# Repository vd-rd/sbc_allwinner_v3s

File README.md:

# Allwinner V3s SBC

This board embeds a SIP (single core 1GHz Cortex-A7 with 64MB DDR2) with AXP203 PMIC, IO headers and microSD/eMMC storage.

Board overview (draft):
[TBD]

## Board features
| Characteristic | Description |
| --- | --- |
| Dimensions | 60mm x 40mm |
| Processor | Allwinner V3s Cortex-A7 @1GHz |
| Oscillators | 32.768kHz slow click, 24MHz main clock |
| RAM | 512Mb embedded DDR2 memory |
| Storage | SPI Flash/microSD |
| USB | 1 microUSB OTG |
| Ethernet | 10/100M PHY with pins on header |
| Supply | Power path between USB/Vin/Battery, 5V max |

## Notes and observations

### Expansions
The board features a number of connectors. They expose various buses for expansions:
 * 1 SPI port
 * 2 UART ports
 * 1 I2C port
 * 2 ADC enabled pins
 * 18bit parallel LCD interface
 * Ethernet signals with status LEDs

The connectors are organized in consistent locations present on the other SBCs i have developed.
 * J100 connector - 2.54mm 2x18 header with standard Apollo IoT pinout
 * J200 connector - 1.27mm 2x04 header with ethernet signals
 * J300 connector - 1.27mm 2x05 header with analog audio I/O signals
 * J500 connector - 1.27mm 2x20 header with parallel LCD interface signals

Check expansions section for example daughter cards with added functionality

### Boot process
The board has two boot strategies depending on component configuration. If the SPI flash memory is not used, the BROM uses the MicroSD as boot source and loads UBoot from there.
If the SPI flash is populated, UBoot with a minimal Kernel and Busybox can be stored as recovery environment or main application.

### LCD connector
Most of port D signals are mapped to the LCD connector. if LCD is not used they can be muxed as GPIO or other functions upon editing the DT overlay.

### AXP203
AXP203 is pin to pin compatible with the more popular AXP209, so they can be easily swapped.

### 1.2V Rail
Two different 1.2V rails are provided to the CPU. This is a deliberate decision to allow fixed CPU internal rail at 1.2V and provide DVFS cappability to 1.2V rail for CPU core.

### Signals on headers
All the signals on the headers, with their initial functions are detailed on the silkscreen on the bottom layer

### Battery usage
The board schematic uses a Diodes AP9211 battery protection IC for safety protections when used toghether with a LiIon battery. If a battery pack with embedded protection and thermistor is used, TH1 and AP9211 can be left unpopulated.

### Expansions
 The board can be combined with several predefined capes that add functionality.
 * [LCD cape](https://github.com/vd-rd/hw_cape_lcd) can be used to add a 3inch LCD/Touch with 800x480px resolution.
 * [GPS cape](https://github.com/vd-rd/hw_cape_gps) adds GPS/GNSS/GLONAS capabilities
 * [GSM cape](https://github.com/vd-rd/hw_cape_gsm) adds GPRS connectivity. 

## Resources
You can find all necesary information to build or evaluate the module here:
   - [View 3D board render](https://a360.co/2GTPupk)
   - [Fabrication files](https://github.com/vd-rd/sbc_alw_v3s/releases)

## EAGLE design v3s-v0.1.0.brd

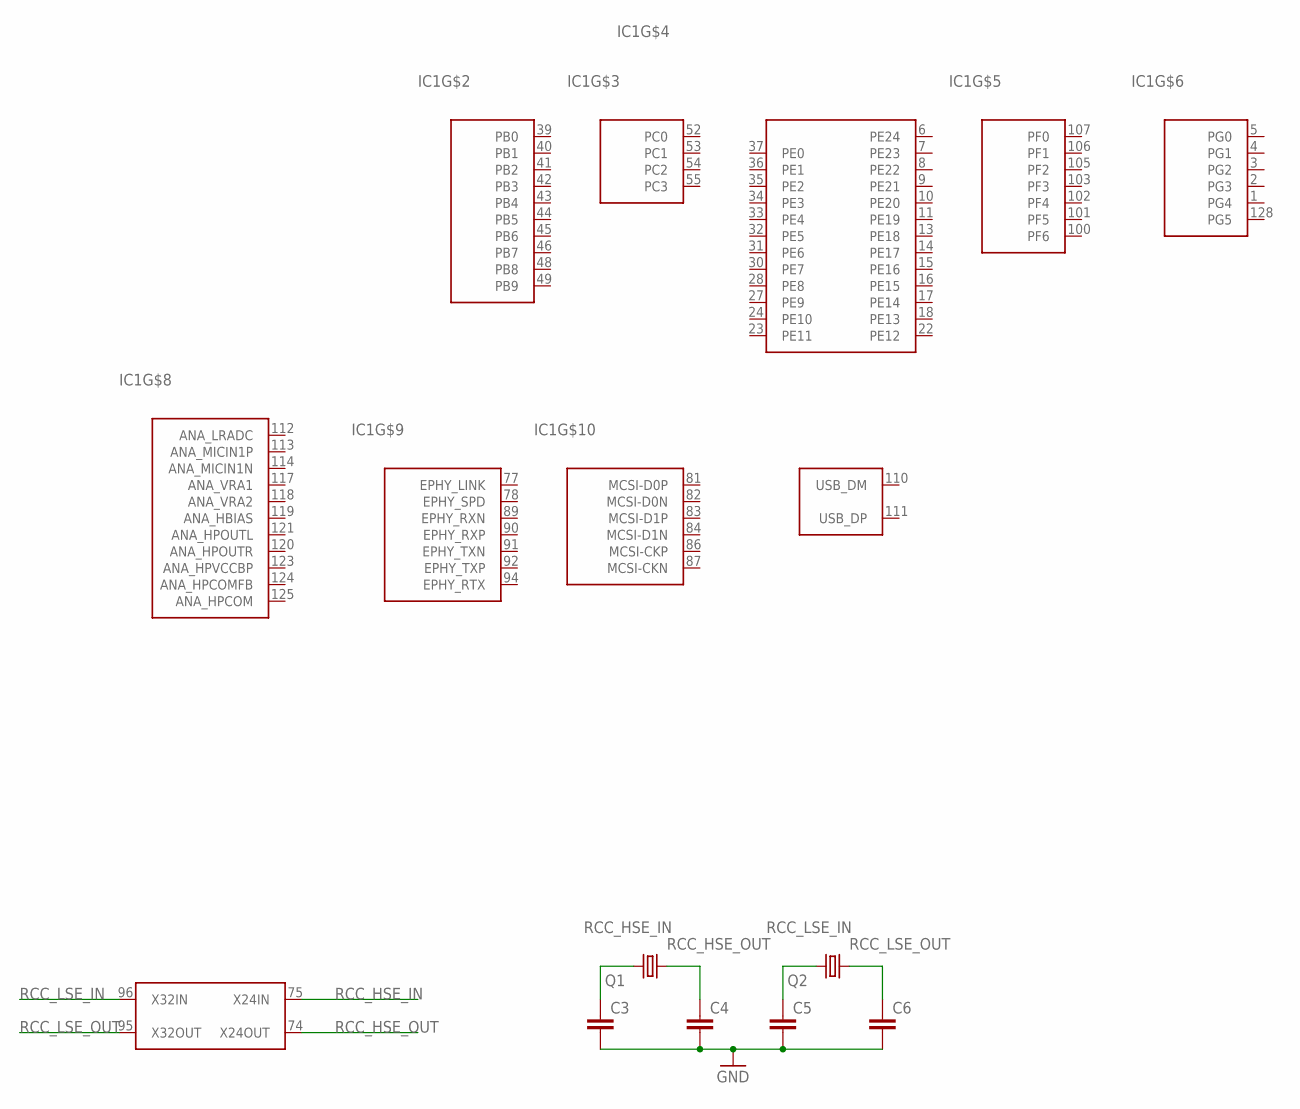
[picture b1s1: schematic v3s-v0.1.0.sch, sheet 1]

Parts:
C3, C4, C5, C6: C-EUC0402; C0402
IC1: V3S; QFP-128
Q1: KX-7; 3.2X2.5_KX-7
Q2: KX-327-NHF; 3.2X1.5

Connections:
GND: C3.2, C4.2, C5.2, C6.2; also elsewhere on the board
RCC_HSE_IN: C3.1, IC1.75 (X24IN), Q1.3 (2)
RCC_HSE_OUT: C4.1, IC1.74 (X24OUT), Q1.1
RCC_LSE_IN: C5.1, IC1.96 (X32IN), Q2.2
RCC_LSE_OUT: C6.1, IC1.95 (X32OUT), Q2.1

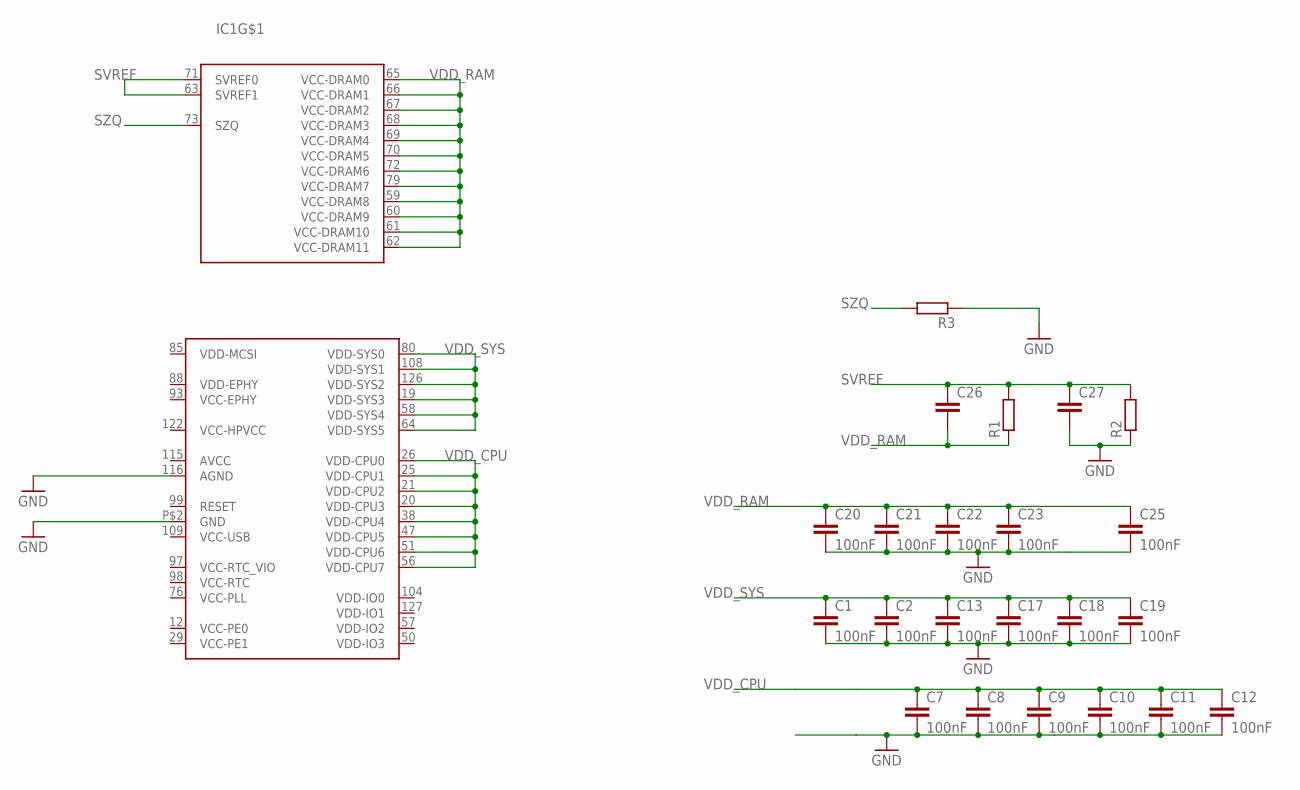
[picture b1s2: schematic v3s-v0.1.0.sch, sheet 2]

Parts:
C1, C2, C7, C8, C9, C10, C11, C12, C13, C17, C18, C19, C20, C21, C22, C23, C25: 100nF; C0402
C26, C27: C-EUC0402; C0402
IC1: V3S; QFP-128
R1, R2, R3: R-EU_R0402; R0402

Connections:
GND: C1.2, C2.2, C7.2, C8.2, C9.2, C10.2, C11.2, C12.2, C13.2, C17.2, C18.2, C19.2, C20.2, C21.2, C22.2, C23.2, C25.2, C27.2, IC1.116 (AGND), IC1.P$2 (GND), R2.1, R3.1; also elsewhere on the board
SVREF: C26.1, C27.1, IC1.63 (SVREF1), IC1.71 (SVREF0), R1.2, R2.2
SZQ: IC1.73 (SZQ), R3.2
VDD_CPU: C7.1, C8.1, C9.1, C10.1, C11.1, C12.1, IC1.20 (VDD-CPU3), IC1.21 (VDD-CPU2), IC1.25 (VDD-CPU1), IC1.26 (VDD-CPU0), IC1.38 (VDD-CPU4), IC1.47 (VDD-CPU5), IC1.51 (VDD-CPU6), IC1.56 (VDD-CPU7)
VDD_RAM: C20.1, C21.1, C22.1, C23.1, C25.1, C26.2, IC1.59 (VCC-DRAM8), IC1.60 (VCC-DRAM9), IC1.61 (VCC-DRAM10), IC1.62 (VCC-DRAM11), IC1.65 (VCC-DRAM0), IC1.66 (VCC-DRAM1), IC1.67 (VCC-DRAM2), IC1.68 (VCC-DRAM3), IC1.69 (VCC-DRAM4), IC1.70 (VCC-DRAM5), IC1.72 (VCC-DRAM6), IC1.79 (VCC-DRAM7), R1.1
VDD_SYS: C1.1, C2.1, C13.1, C17.1, C18.1, C19.1, IC1.19 (VDD-SYS3), IC1.58 (VDD-SYS4), IC1.64 (VDD-SYS5), IC1.80 (VDD-SYS0), IC1.108 (VDD-SYS1), IC1.126 (VDD-SYS2)

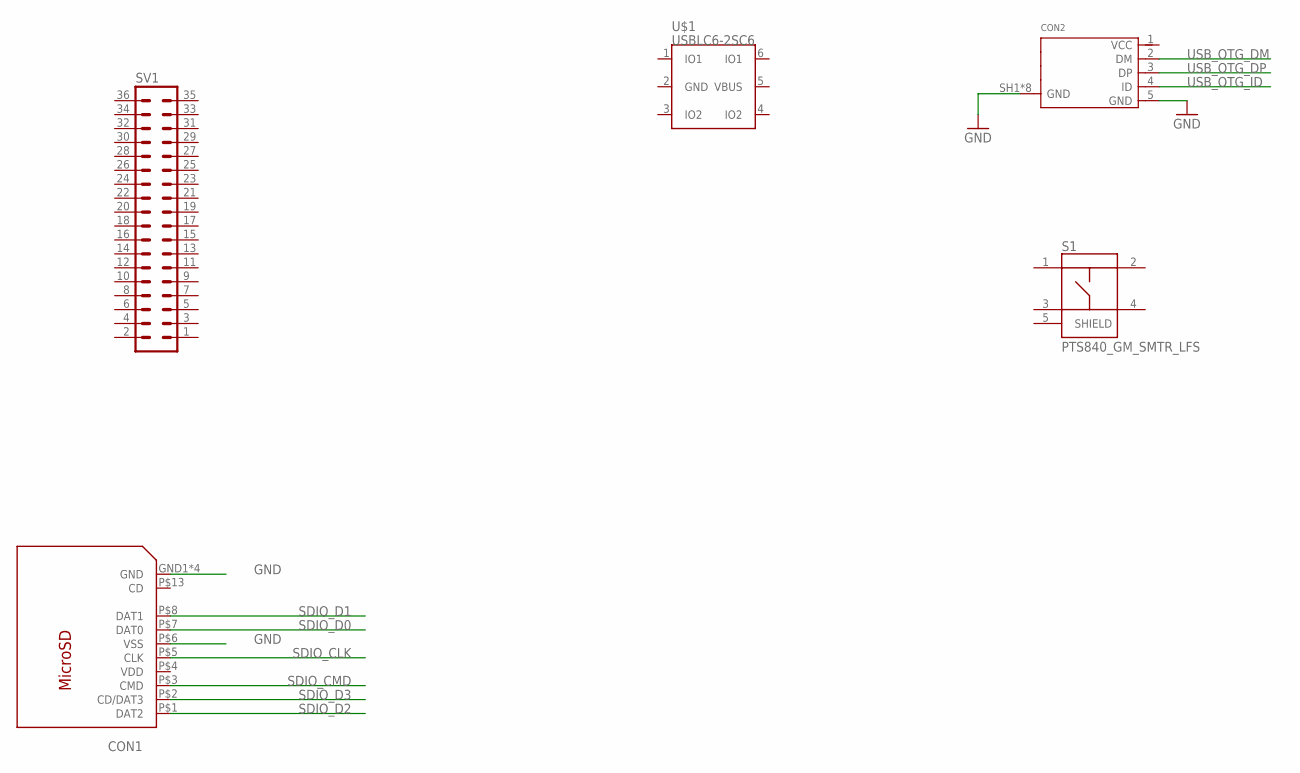
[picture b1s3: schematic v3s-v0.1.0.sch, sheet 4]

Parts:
CON1: 112J-TXAR; 112J
CON2: 10118194-0001LF; 10118194
S1: PTS840_GM_SMTR_LFS; SW_PTS840GMSMTRLFS
SV1: MA18-2
U$1: USBLC6-2SC6; SOT95P280X110-6

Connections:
GND: CON1.GND1 (GND), CON1.GND2 (GND), CON1.GND3 (GND), CON1.GND4 (GND), CON1.P$6 (VSS), CON2.5 (GND), CON2.SH1 (GND), CON2.SH2 (GND), CON2.SH3 (GND), CON2.SH4 (GND), CON2.SH5 (GND), CON2.SH6 (GND), CON2.SH7 (GND), CON2.SH8 (GND); also elsewhere on the board
SDIO_CLK: CON1.P$5 (CLK)
SDIO_CMD: CON1.P$3 (CMD)
SDIO_D0: CON1.P$7 (DAT0)
SDIO_D1: CON1.P$8 (DAT1)
SDIO_D2: CON1.P$1 (DAT2)
SDIO_D3: CON1.P$2 (CD/DAT3)
USB_OTG_DM: CON2.2 (DM)
USB_OTG_DP: CON2.3 (DP)
USB_OTG_ID: CON2.4 (ID)

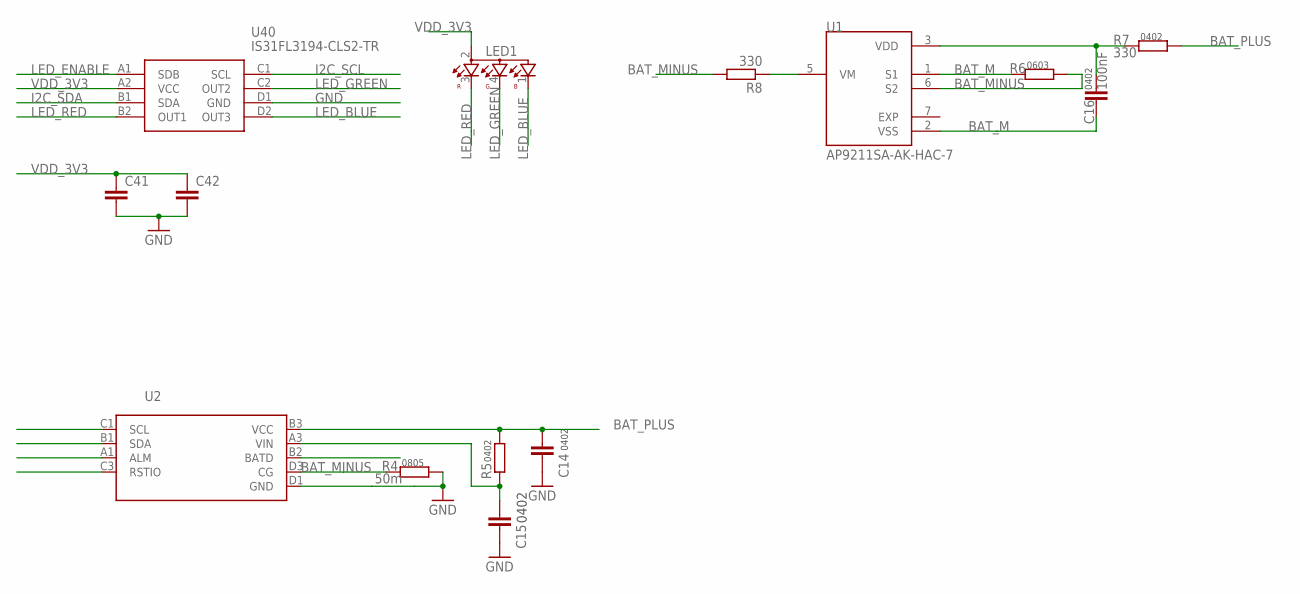
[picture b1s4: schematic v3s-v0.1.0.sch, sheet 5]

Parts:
C14, C15, C41, C42: C-EUC0402; C0402
C16: 100nF; C0402
LED1: OSTB1204C1E; 321015RGB
R4: 50m; R0805
R5: R-EU_R0402; R0402
R6: R-EU_R0603; R0603
R7, R8: 330; R0402
U1: AP9211SA-AK-HAC-7; DFN200X300X60-7N
U2: STC3115; BGA12C40P4X3_137X201X65
U40: IS31FL3194-CLS2-TR; BGA8C40P2X4_99X159X42

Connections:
BAT_M: C16.2, R6.2, U1.1 (S1), U1.2 (VSS)
BAT_MINUS: R4.2, R6.1, R8.2, U1.6 (S2), U2.D3 (CG)
BAT_PLUS: C14.1, R5.2, R7.1, U2.B3 (VCC)
EXP: U1.7 (EXP)
GND: C14.2, C15.2, C41.2, C42.2, R4.1, U2.D1 (GND), U40.D1 (GND); also elsewhere on the board
I2C_SCL: U40.C1 (SCL)
I2C_SDA: U40.B1 (SDA)
LED_BLUE: LED1.1, U40.D2 (OUT3)
LED_ENABLE: U40.A1 (SDB)
LED_GREEN: LED1.4, U40.C2 (OUT2)
LED_RED: LED1.3, U40.B2 (OUT1)
unnamed: C16.1, R7.2, U1.3 (VDD)
unnamed: C15.1, R5.1, U2.A3 (VIN)
unnamed: R8.1, U1.5 (VM)
VDD_3V3: C41.1, C42.1, LED1.2, U40.A2 (VCC)

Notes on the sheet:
0805
0402
0603

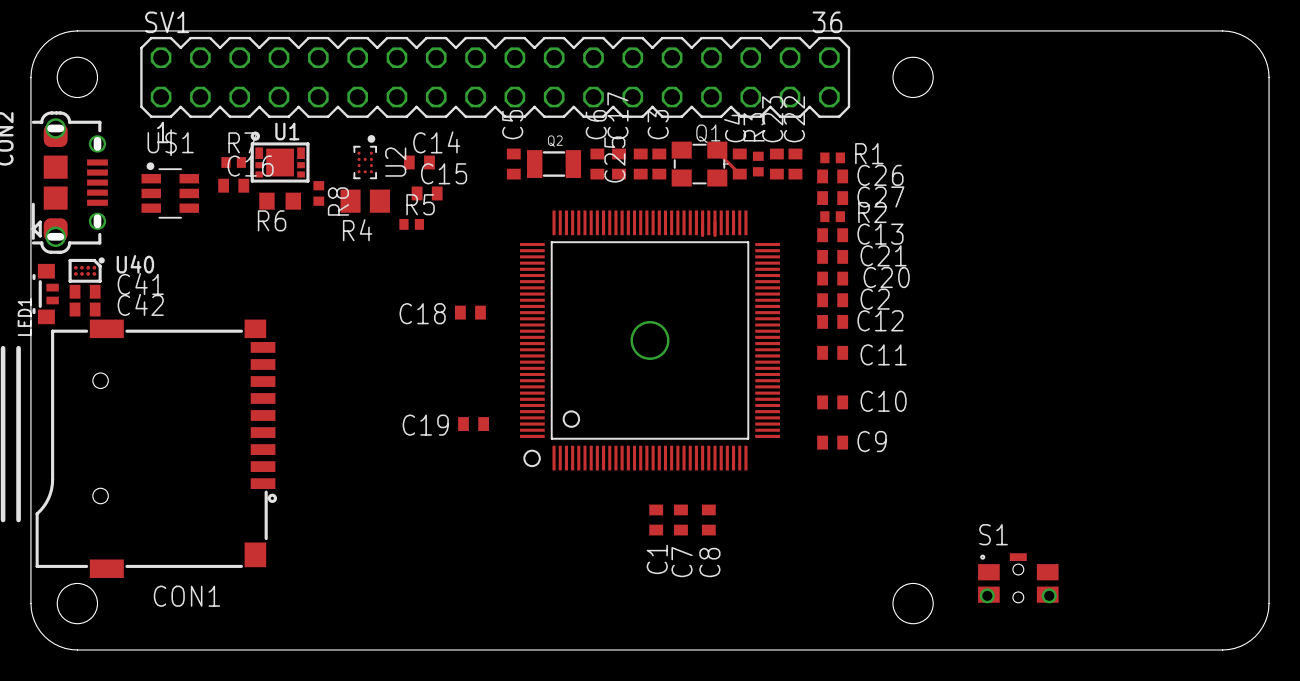
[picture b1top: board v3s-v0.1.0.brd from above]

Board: 4 copper layers, 80.0 x 40.0 mm, 48 parts (0 on the bottom side), 20 nets.

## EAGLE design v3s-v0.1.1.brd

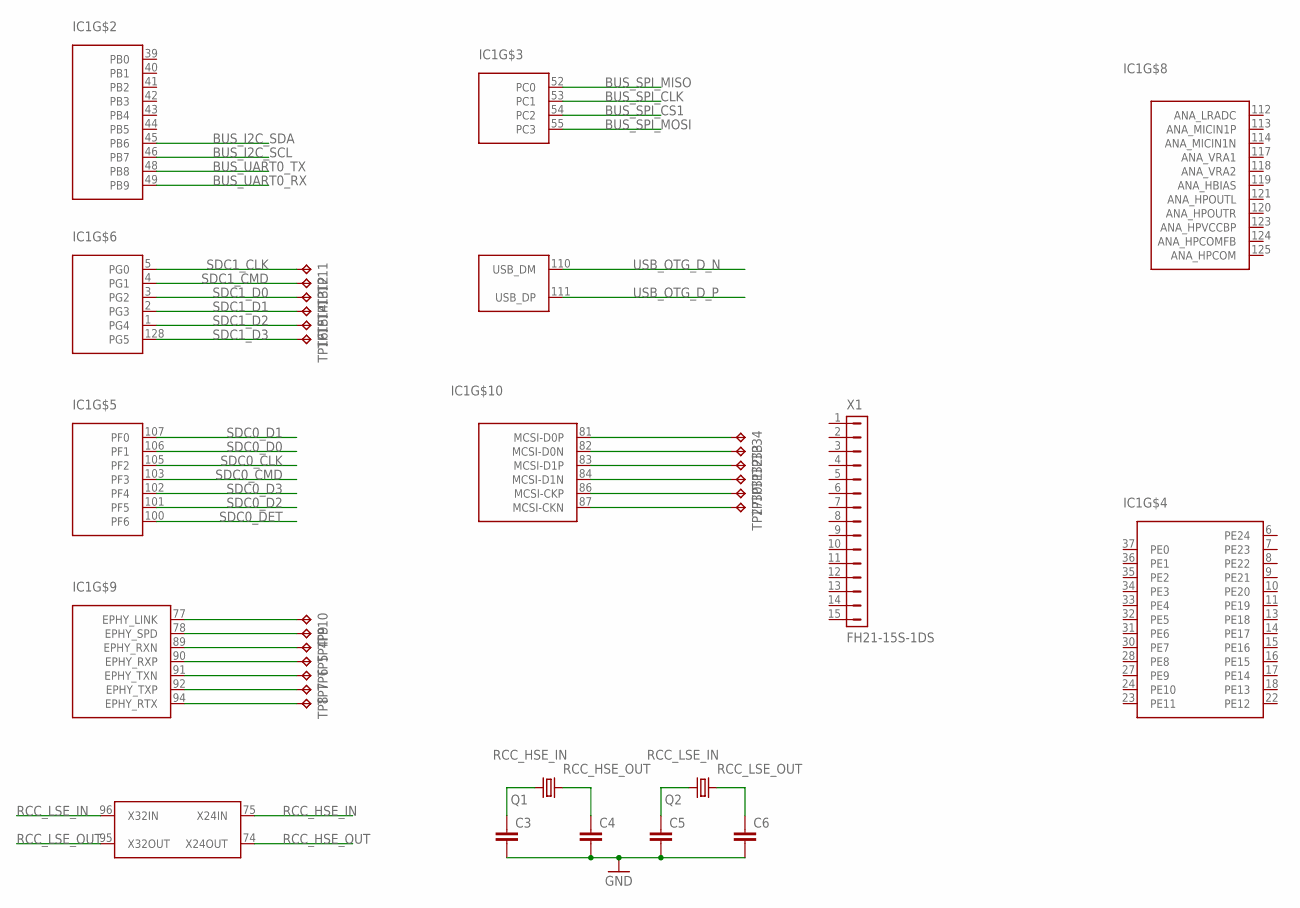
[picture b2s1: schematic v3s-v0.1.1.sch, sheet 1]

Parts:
C3, C4, C5, C6: C-EUC0402; C0402
IC1: V3S; QFP-128
Q1: KX-7; 3.2X2.5_KX-7
Q2: KX-327-NHF; 3.2X1.5
TP4, TP5, TP6, TP7, TP8, TP9, TP10, TP11, TP12, TP13, TP14, TP15, TP16, TP27, TP30, TP31, TP32, TP33, TP34: TPB1,27; B1,27
X1: FH21-15S-1DS

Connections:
BUS_I2C_SCL: IC1.46 (PB7); also elsewhere on the board
BUS_I2C_SDA: IC1.45 (PB6); also elsewhere on the board
BUS_SPI_CLK: IC1.53 (PC1); also elsewhere on the board
BUS_SPI_CS1: IC1.54 (PC2)
BUS_SPI_MISO: IC1.52 (PC0); also elsewhere on the board
BUS_SPI_MOSI: IC1.55 (PC3); also elsewhere on the board
BUS_UART0_RX: IC1.49 (PB9)
BUS_UART0_TX: IC1.48 (PB8)
GND: C3.2, C4.2, C5.2, C6.2; also elsewhere on the board
unnamed: IC1.78 (EPHY_SPD), TP9.TP
unnamed: IC1.77 (EPHY_LINK), TP10.TP
unnamed: IC1.94 (EPHY_RTX), TP8.TP
unnamed: IC1.92 (EPHY_TXP), TP7.TP
unnamed: IC1.91 (EPHY_TXN), TP6.TP
unnamed: IC1.90 (EPHY_RXP), TP5.TP
unnamed: IC1.89 (EPHY_RXN), TP4.TP
unnamed: IC1.81 (MCSI-D0P), TP34.TP
unnamed: IC1.82 (MCSI-D0N), TP33.TP
unnamed: IC1.83 (MCSI-D1P), TP32.TP
unnamed: IC1.84 (MCSI-D1N), TP31.TP
unnamed: IC1.86 (MCSI-CKP), TP30.TP
unnamed: IC1.87 (MCSI-CKN), TP27.TP
RCC_HSE_IN: C3.1, IC1.75 (X24IN), Q1.3 (2)
RCC_HSE_OUT: C4.1, IC1.74 (X24OUT), Q1.1
RCC_LSE_IN: C5.1, IC1.96 (X32IN), Q2.2
RCC_LSE_OUT: C6.1, IC1.95 (X32OUT), Q2.1
SDC0_CLK: IC1.105 (PF2); also elsewhere on the board
SDC0_CMD: IC1.103 (PF3); also elsewhere on the board
SDC0_D0: IC1.106 (PF1); also elsewhere on the board
SDC0_D1: IC1.107 (PF0); also elsewhere on the board
SDC0_D2: IC1.101 (PF5); also elsewhere on the board
SDC0_D3: IC1.102 (PF4); also elsewhere on the board
SDC0_DET: IC1.100 (PF6); also elsewhere on the board
SDC1_CLK: IC1.5 (PG0), TP11.TP; also elsewhere on the board
SDC1_CMD: IC1.4 (PG1), TP12.TP; also elsewhere on the board
SDC1_D0: IC1.3 (PG2), TP13.TP; also elsewhere on the board
SDC1_D1: IC1.2 (PG3), TP14.TP; also elsewhere on the board
SDC1_D2: IC1.1 (PG4), TP15.TP; also elsewhere on the board
SDC1_D3: IC1.128 (PG5), TP16.TP; also elsewhere on the board
USB_OTG_D_N: IC1.110 (USB_DM); also elsewhere on the board
USB_OTG_D_P: IC1.111 (USB_DP); also elsewhere on the board

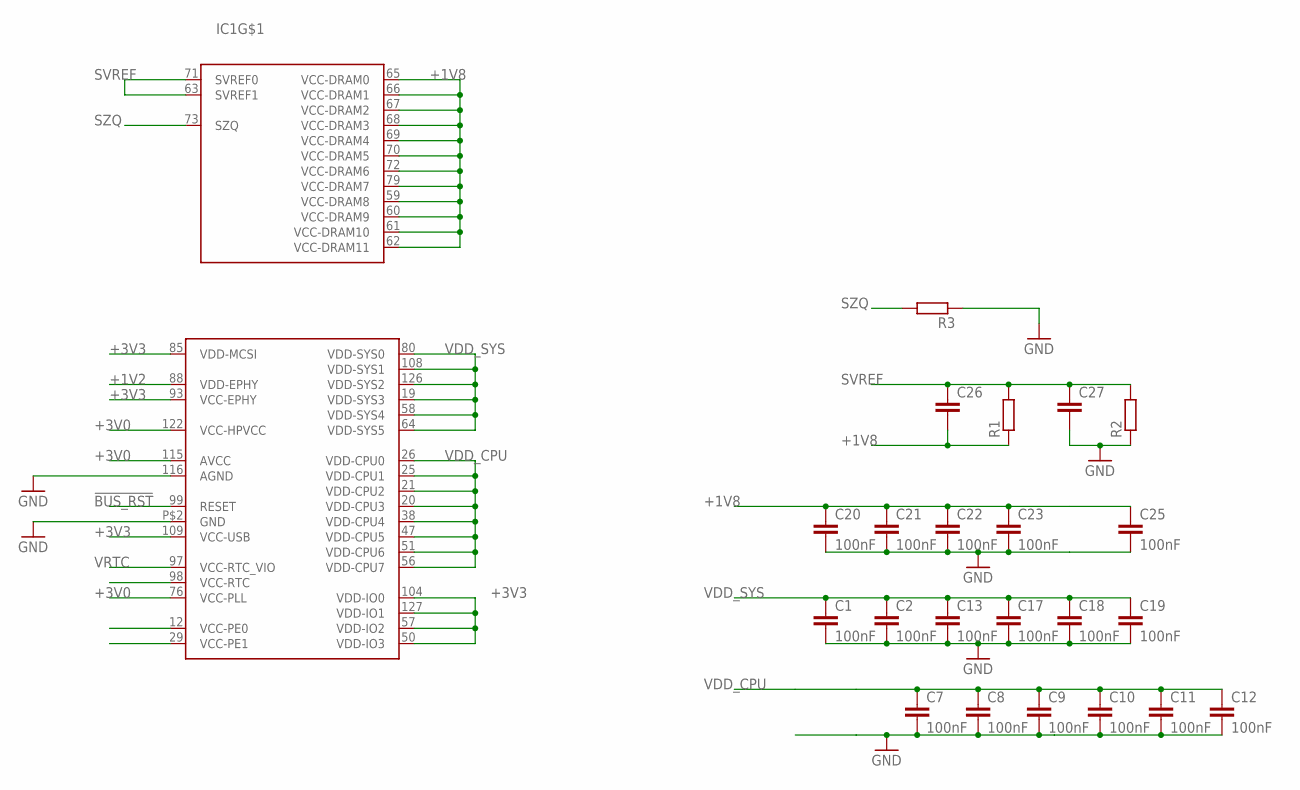
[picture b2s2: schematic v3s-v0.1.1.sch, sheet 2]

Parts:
C1, C2, C7, C8, C9, C10, C11, C12, C13, C17, C18, C19, C20, C21, C22, C23, C25: 100nF; C0402
C26, C27: C-EUC0402; C0402
IC1: V3S; QFP-128
R1, R2, R3: R-EU_R0402; R0402

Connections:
!BUS_RST: IC1.99 (RESET); also elsewhere on the board
+1V2: IC1.88 (VDD-EPHY); also elsewhere on the board
+1V8: C20.1, C21.1, C22.1, C23.1, C25.1, C26.2, IC1.59 (VCC-DRAM8), IC1.60 (VCC-DRAM9), IC1.61 (VCC-DRAM10), IC1.62 (VCC-DRAM11), IC1.65 (VCC-DRAM0), IC1.66 (VCC-DRAM1), IC1.67 (VCC-DRAM2), IC1.68 (VCC-DRAM3), IC1.69 (VCC-DRAM4), IC1.70 (VCC-DRAM5), IC1.72 (VCC-DRAM6), IC1.79 (VCC-DRAM7), R1.1; also elsewhere on the board
+3V0: IC1.76 (VCC-PLL), IC1.115 (AVCC), IC1.122 (VCC-HPVCC)
+3V3: IC1.50 (VDD-IO3), IC1.57 (VDD-IO2), IC1.85 (VDD-MCSI), IC1.93 (VCC-EPHY), IC1.104 (VDD-IO0), IC1.109 (VCC-USB), IC1.127 (VDD-IO1); also elsewhere on the board
GND: C1.2, C2.2, C7.2, C8.2, C9.2, C10.2, C11.2, C12.2, C13.2, C17.2, C18.2, C19.2, C20.2, C21.2, C22.2, C23.2, C25.2, C27.2, IC1.116 (AGND), IC1.P$2 (GND), R2.1, R3.1; also elsewhere on the board
SVREF: C26.1, C27.1, IC1.63 (SVREF1), IC1.71 (SVREF0), R1.2, R2.2
SZQ: IC1.73 (SZQ), R3.2
VDD_CPU: C7.1, C8.1, C9.1, C10.1, C11.1, C12.1, IC1.20 (VDD-CPU3), IC1.21 (VDD-CPU2), IC1.25 (VDD-CPU1), IC1.26 (VDD-CPU0), IC1.38 (VDD-CPU4), IC1.47 (VDD-CPU5), IC1.51 (VDD-CPU6), IC1.56 (VDD-CPU7)
VDD_SYS: C1.1, C2.1, C13.1, C17.1, C18.1, C19.1, IC1.19 (VDD-SYS3), IC1.58 (VDD-SYS4), IC1.64 (VDD-SYS5), IC1.80 (VDD-SYS0), IC1.108 (VDD-SYS1), IC1.126 (VDD-SYS2)
VRTC: IC1.97 (VCC-RTC_VIO)

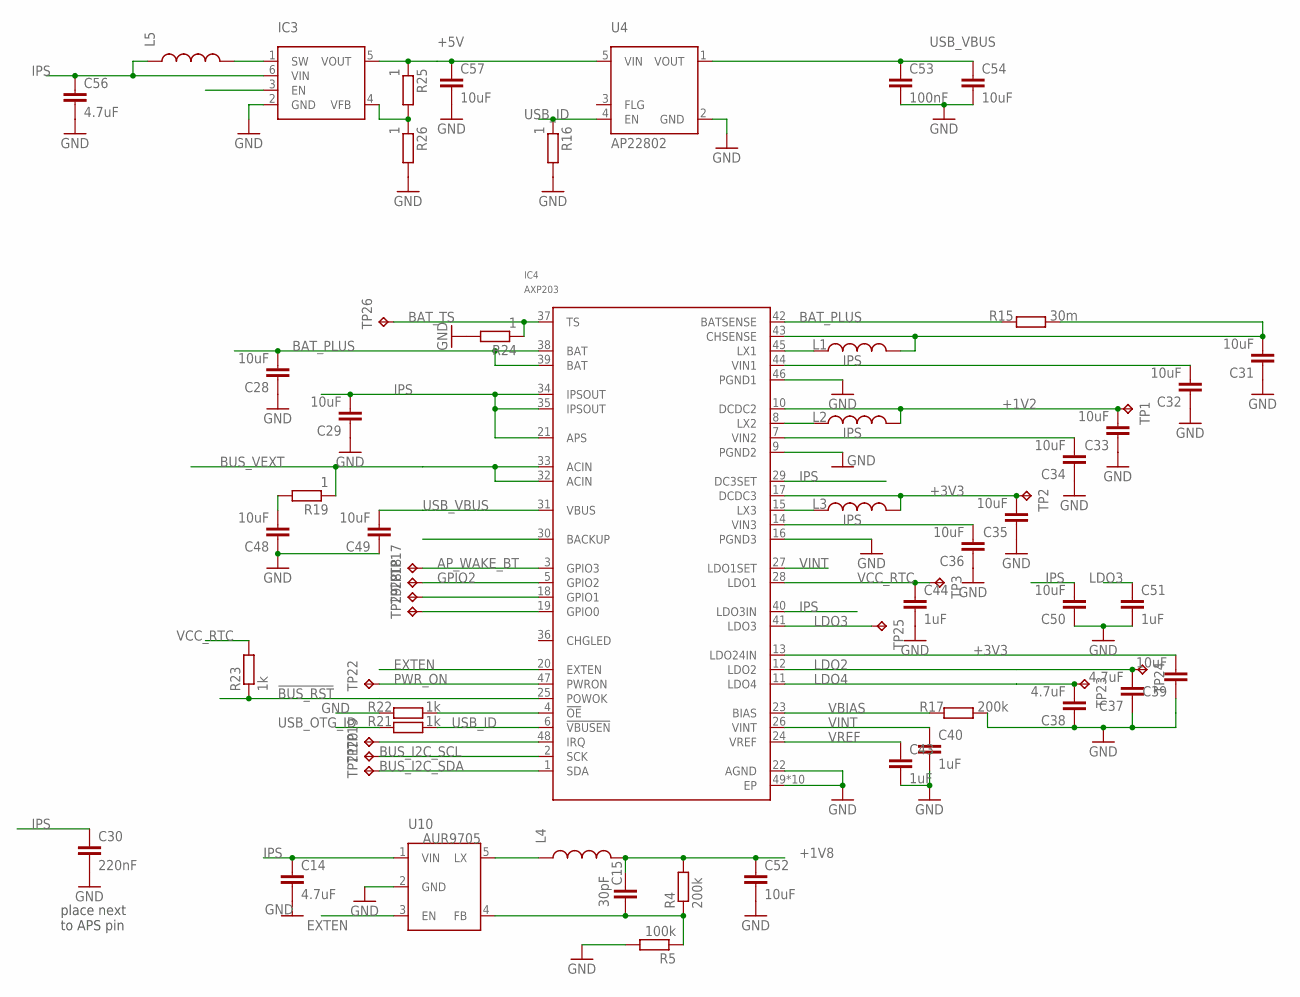
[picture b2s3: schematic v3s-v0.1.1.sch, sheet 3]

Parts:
C14, C37, C38, C56: 4.7uF; C0603
C15: 30pF; C0402
C28, C29, C31, C32, C33, C34, C35, C36, C39, C48, C49, C50, C52, C54, C57: 10uF; C0603
C30: 220nF; C0402
C40, C43, C44, C51: 1uF; C0402
C53: 100nF; C0402
IC3: MCP1640; SOT95P280X110-6
IC4: AXP203; QFN40P600X600X80-49T405
L1, L2, L3, L4, L5: DJNR3015; L3230M
R4, R17: 200k; R0402
R5: 100k; R0402
R15: 30m; R0805
R16, R19, R24, R25, R26: 1; R0402
R21, R22, R23: 1k; R0402
TP1, TP2, TP3, TP17, TP18, TP19, TP20, TP21, TP22, TP23, TP24, TP25, TP26, TP28, TP29: TPB1,27; B1,27
U4: AP22802; SOT25
U10: AUR9705; SOT25

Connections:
!BUS_RST: IC4.25 (POWOK), R23.1; also elsewhere on the board
+1V2: C33.2, IC4.10 (DCDC2), L2.2, TP1.TP; also elsewhere on the board
+1V8: C15.1, C52.1, L4.2, R4.2; also elsewhere on the board
+3V3: C35.2, C39.2, IC4.13 (LDO24IN), IC4.17 (DCDC3), L3.2, TP2.TP; also elsewhere on the board
+5V: C57.1, IC3.5 (VOUT), R25.1, U4.5 (VIN)
AP_WAKE_BT: IC4.3 (GPIO3), TP17.TP
BAT_PLUS: C28.2, IC4.38 (BAT), IC4.39 (BAT), IC4.42 (BATSENSE), R15.1; also elsewhere on the board
BAT_TS: IC4.37 (TS), R24.1, TP26.TP
BUS_I2C_SCL: IC4.2 (SCK), TP20.TP; also elsewhere on the board
BUS_I2C_SDA: IC4.1 (SDA), TP21.TP; also elsewhere on the board
BUS_VEXT: IC4.32 (ACIN), IC4.33 (ACIN), R19.1; also elsewhere on the board
EXTEN: IC4.20 (EXTEN), U10.3 (EN)
GND: C14.2, C28.1, C29.1, C30.2, C31.1, C32.1, C33.1, C34.1, C35.1, C36.1, C37.1, C38.1, C39.1, C40.2, C43.2, C44.2, C48.1, C49.1, C50.1, C51.2, C52.2, C53.2, C54.2, C56.2, C57.2, IC3.2 (GND), IC4.9 (PGND2), IC4.16 (PGND3), IC4.22 (AGND), IC4.46 (PGND1), IC4.49 (EP), IC4.P$1 (EP), IC4.P$2 (EP), IC4.P$3 (EP), IC4.P$4 (EP), IC4.P$5 (EP), IC4.P$6 (EP), IC4.P$7 (EP), IC4.P$8 (EP), IC4.P$9 (EP), R5.2, R16.2, R17.2, R22.1, R24.2, R26.2, U4.2 (GND), U10.2 (GND); also elsewhere on the board
GPIO2: IC4.5 (GPIO2), TP18.TP
IPS: C14.1, C29.2, C30.1, C32.2, C34.2, C36.2, C50.2, C56.1, IC3.6 (VIN), IC4.7 (VIN2), IC4.14 (VIN3), IC4.21 (APS), IC4.29 (DC3SET), IC4.34 (IPSOUT), IC4.35 (IPSOUT), IC4.40 (LDO3IN), IC4.44 (VIN1), L5.1, U10.1 (VIN)
LDO2: C37.2, IC4.12 (LDO2), TP24.TP
LDO3: C51.1, IC4.41 (LDO3), TP25.TP
LDO4: C38.2, IC4.11 (LDO4), TP23.TP
unnamed: IC4.15 (LX3), L3.1
unnamed: IC4.18 (GPIO1), TP28.TP
unnamed: IC4.19 (GPIO0), TP29.TP
unnamed: L4.1, U10.5 (LX)
unnamed: C15.2, R4.1, R5.1, U10.4 (FB)
unnamed: IC3.1 (SW), L5.2
unnamed: IC4.8 (LX2), L2.1
unnamed: IC3.4 (VFB), R25.2, R26.1
unnamed: IC4.45 (LX1), L1.1
unnamed: C31.2, IC4.43 (CHSENSE), L1.2, R15.2
unnamed: IC4.48 (IRQ), TP19.TP
unnamed: IC4.4 (!OE), R22.2
unnamed: C48.2, R19.2
PWR_ON: IC4.47 (PWRON), TP22.TP
USB_ID: IC4.6 (!VBUSEN), R16.1, R21.2, U4.4 (EN)
USB_OTG_ID: R21.1; also elsewhere on the board
USB_VBUS: C49.2, C53.1, C54.1, IC4.31 (VBUS), U4.1 (VOUT); also elsewhere on the board
VBIAS: IC4.23 (BIAS), R17.1
VCC_RTC: C44.1, IC4.28 (LDO1), R23.2, TP3.TP
VINT: C40.1, IC4.26 (VINT), IC4.27 (LDO1SET)
VREF: C43.1, IC4.24 (VREF)

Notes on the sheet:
place next to APS pin

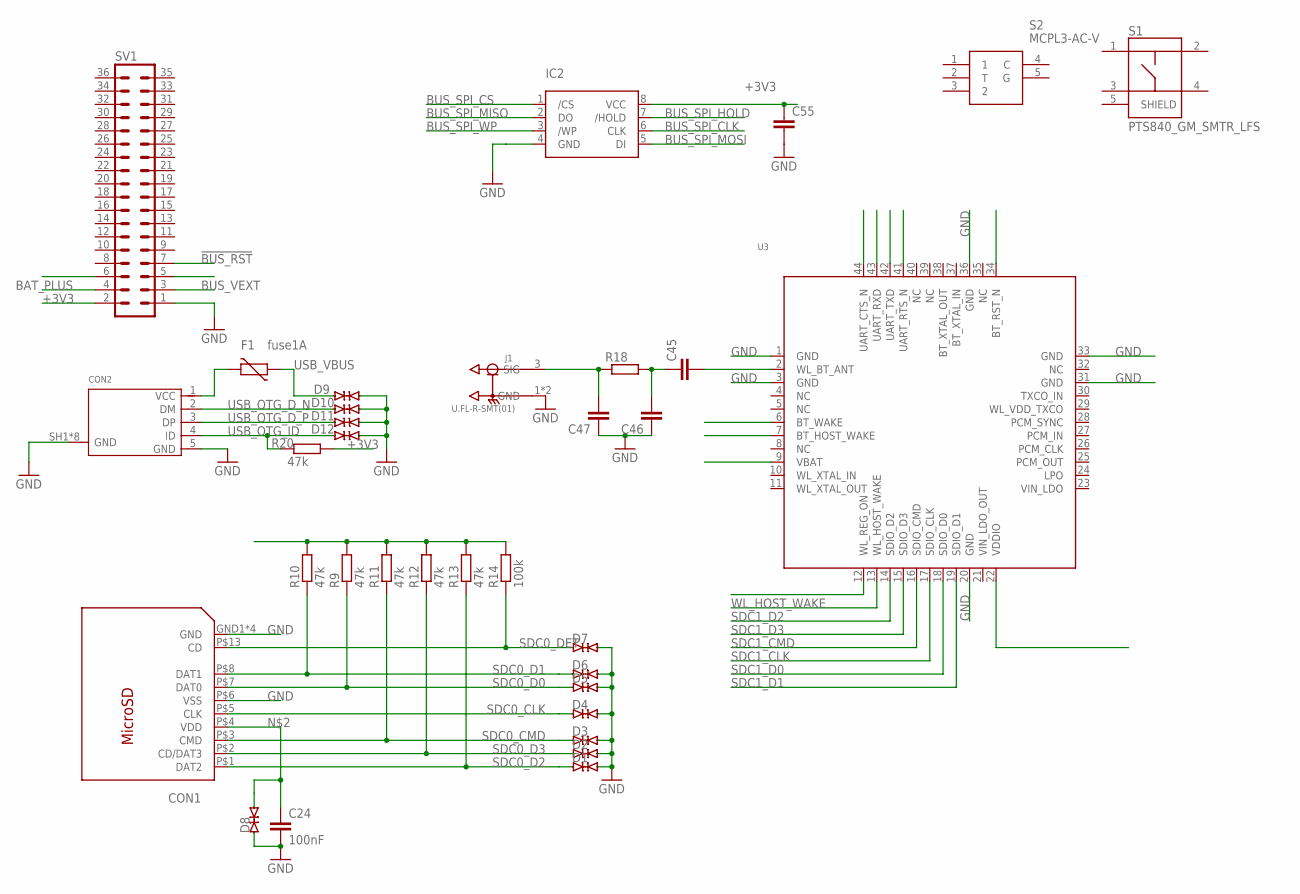
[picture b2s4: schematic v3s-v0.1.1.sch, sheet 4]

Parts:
C24: 100nF; C0402
C45, C46, C47: C-EUC0402; C0402
C55: C-EUC0603; C0603
CON1: 112J-TXAR; 112J
CON2: 10118194-0001LF; 10118194
D1, D2, D3, D4, D5, D6, D7, D8, D9, D10, D11, D12: ESD9B5.0ST5G; SOD1006X40
F1: fuse1A; CT/CN0603
IC2: W25Q128JV; SO08-208
J1: U.FL-R-SMT(01); HRS_U.FL-R-SMT(01)
R9, R10, R11, R12, R13, R20: 47k; R0402
R14: 100k; R0402
R18: R-EU_R0402; R0402
S1: PTS840_GM_SMTR_LFS; SW_PTS840GMSMTRLFS
S2: MCPL3-AC-V
SV1: MA18-2
U3: RTL8723BS; QFN90P1200X1200X100-44

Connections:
!BUS_RST: SV1.7; also elsewhere on the board
+3V3: C55.1, IC2.8 (VCC), R20.2, SV1.2; also elsewhere on the board
BAT_PLUS: SV1.4; also elsewhere on the board
BUS_SPI_CLK: IC2.6 (CLK); also elsewhere on the board
BUS_SPI_CS: IC2.1 (/CS)
BUS_SPI_HOLD: IC2.7 (/HOLD)
BUS_SPI_MISO: IC2.2 (DO); also elsewhere on the board
BUS_SPI_MOSI: IC2.5 (DI); also elsewhere on the board
BUS_SPI_WP: IC2.3 (/WP)
BUS_VEXT: SV1.3; also elsewhere on the board
GND: C24.2, C46.1, C47.1, C55.2, CON1.GND1 (GND), CON1.GND2 (GND), CON1.GND3 (GND), CON1.GND4 (GND), CON1.P$6 (VSS), CON2.5 (GND), CON2.SH1 (GND), CON2.SH2 (GND), CON2.SH3 (GND), CON2.SH4 (GND), CON2.SH5 (GND), CON2.SH6 (GND), CON2.SH7 (GND), CON2.SH8 (GND), D1.2 (C), D2.2 (C), D3.2 (C), D4.2 (C), D5.2 (C), D6.2 (C), D7.2 (C), D8.1 (A), D9.2 (C), D10.2 (C), D11.2 (C), D12.2 (C), IC2.4 (GND), J1.1 (GND), J1.2 (GND), SV1.1, U3.1 (GND), U3.3 (GND), U3.20 (GND), U3.31 (GND), U3.33 (GND), U3.36 (GND); also elsewhere on the board
unnamed: R9.2, R10.2, R11.2, R12.2, R13.2, R14.2
unnamed: C24.1, CON1.P$4 (VDD), D8.2 (C)
unnamed: CON2.1 (VCC), F1.2
unnamed: C45.2, U3.2 (WL_BT_ANT)
unnamed: C45.1, C46.2, R18.2
unnamed: C47.2, J1.3 (SIG), R18.1
SDC0_CLK: CON1.P$5 (CLK), D4.1 (A); also elsewhere on the board
SDC0_CMD: CON1.P$3 (CMD), D3.1 (A), R11.1; also elsewhere on the board
SDC0_D0: CON1.P$7 (DAT0), D5.1 (A), R9.1; also elsewhere on the board
SDC0_D1: CON1.P$8 (DAT1), D6.1 (A), R10.1; also elsewhere on the board
SDC0_D2: CON1.P$1 (DAT2), D1.1 (A), R13.1; also elsewhere on the board
SDC0_D3: CON1.P$2 (CD/DAT3), D2.1 (A), R12.1; also elsewhere on the board
SDC0_DET: CON1.P$13 (CD), D7.1 (A), R14.1; also elsewhere on the board
SDC1_CLK: U3.17 (SDIO_CLK); also elsewhere on the board
SDC1_CMD: U3.16 (SDIO_CMD); also elsewhere on the board
SDC1_D0: U3.18 (SDIO_D0); also elsewhere on the board
SDC1_D1: U3.19 (SDIO_D1); also elsewhere on the board
SDC1_D2: U3.14 (SDIO_D2); also elsewhere on the board
SDC1_D3: U3.15 (SDIO_D3); also elsewhere on the board
USB_OTG_D_N: CON2.2 (DM), D10.1 (A); also elsewhere on the board
USB_OTG_D_P: CON2.3 (DP), D11.1 (A); also elsewhere on the board
USB_OTG_ID: CON2.4 (ID), D12.1 (A), R20.1; also elsewhere on the board
USB_VBUS: D9.1 (A), F1.1; also elsewhere on the board
WL_HOST_WAKE: U3.13 (WL_HOST_WAKE)

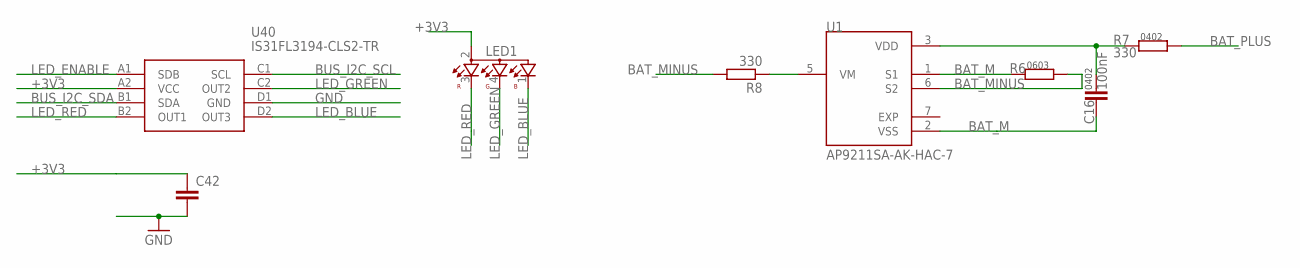
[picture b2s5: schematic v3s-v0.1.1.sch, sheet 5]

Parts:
C16: 100nF; C0402
C42: C-EUC0402; C0402
LED1: OSTB1204C1E; 321015RGB
R6: R-EU_R0603; R0603
R7, R8: 330; R0402
U1: AP9211SA-AK-HAC-7; DFN200X300X60-7N
U40: IS31FL3194-CLS2-TR; BGA8C40P2X4_99X159X42

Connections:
+3V3: C42.1, LED1.2, U40.A2 (VCC); also elsewhere on the board
BAT_M: C16.2, R6.2, U1.1 (S1), U1.2 (VSS)
BAT_MINUS: R6.1, R8.2, U1.6 (S2)
BAT_PLUS: R7.1; also elsewhere on the board
BUS_I2C_SCL: U40.C1 (SCL); also elsewhere on the board
BUS_I2C_SDA: U40.B1 (SDA); also elsewhere on the board
EXP: U1.7 (EXP)
GND: C42.2, U40.D1 (GND); also elsewhere on the board
LED_BLUE: LED1.1, U40.D2 (OUT3)
LED_ENABLE: U40.A1 (SDB)
LED_GREEN: LED1.4, U40.C2 (OUT2)
LED_RED: LED1.3, U40.B2 (OUT1)
unnamed: C16.1, R7.2, U1.3 (VDD)
unnamed: R8.1, U1.5 (VM)

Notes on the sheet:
0603
0402

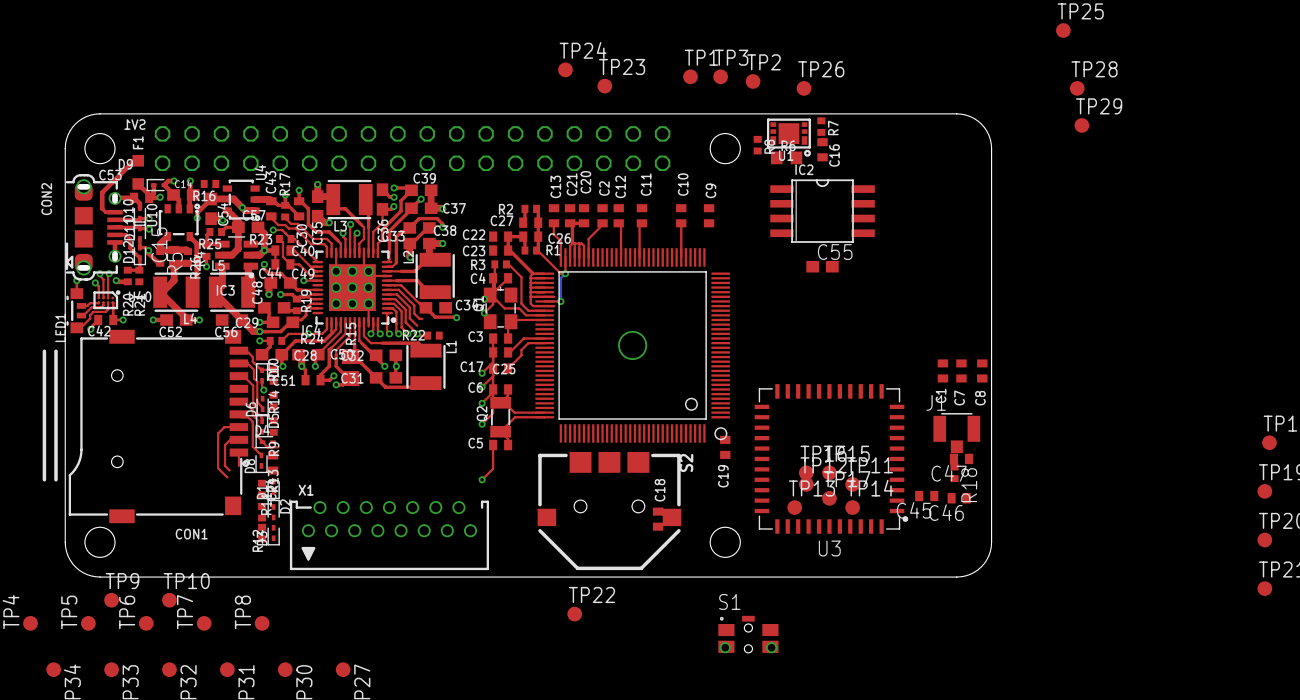
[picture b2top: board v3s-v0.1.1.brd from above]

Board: 4 copper layers, 80.0 x 40.0 mm, 153 parts (1 on the bottom side), 92 nets.

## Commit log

2019-01-22 repo bringup
2019-05-02 project: updated structure
2019-05-15 board: updated flooplan
2019-05-17 board: added nvm storage
2019-05-17 defined power stage
2019-11-22 project: refactor board with new specs
2021-10-04 switch to kicad
2021-10-06 updates on features and layout
2021-10-10 improve component placement
2021-10-16 added proper pmic
2021-10-23 upadted dimensions and component positions
2021-10-23 cosmetic fixes
2021-10-24 swap pmic section with axp203
2021-10-25 added 3d models
2021-10-26 arranged parts for pmic
2021-11-01 routed axp203 and optimized component footprints
2021-11-13 small fixes
2022-01-04 prepare for component reposition
2022-01-10 change component layout
2022-01-10 defined cpu connections
2022-01-11 routed lcd signals
2022-01-14 routed lcd bus
2022-01-16 add layer identification labels
2022-01-25 small layout tweaks
2022-01-29 remove lcd fpc connector
2022-01-30 add datasheet and new lcd connector
2022-02-25 change cpu footprint
2022-03-08 try new component placement
2022-03-24 add axp203 aux parts
2022-03-28 routing work
2022-03-29 added more testpoints
2022-03-30 add 5v otg support components
2022-04-16 add board render
2022-05-03 add spi flash for boot
2022-05-04 finish lcd bus
2022-05-06 prepare wifi section and io exp
2022-05-07 add wifi parts
2022-05-07 add missing 3d models
2022-05-07 add port expander for additional gpio
2022-05-12 define lcd connector pins
2022-05-13 add port expander connections
2022-05-22 fix ethernet header for compatibility
2022-05-26 more routing work
2022-05-26 fix audio connector
2022-05-26 finished routing
2022-06-16 updated board
2022-07-10 prepare first release for fab
2024-03-08 new layout
2024-06-22 simplified the design
2024-10-28 [WIP] Rework power tree
2025-01-10 rework component placement
2026-01-04 prepare for rev2
2026-01-26 placed decoupling caps
2026-04-22 backport changes

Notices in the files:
parts and their libraries:
crystal-geyer_V1_0: Copyright: Geyer-Electronic
